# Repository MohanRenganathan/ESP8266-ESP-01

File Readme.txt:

This repository contains files related to ESP8266 model ESP-01

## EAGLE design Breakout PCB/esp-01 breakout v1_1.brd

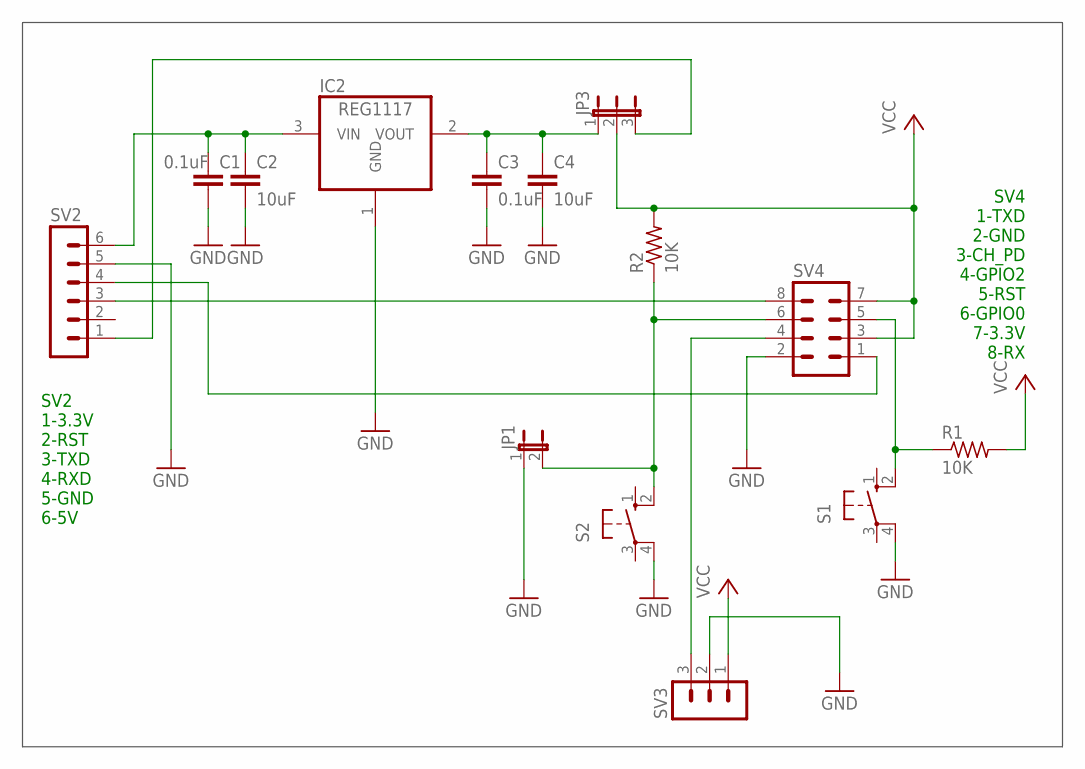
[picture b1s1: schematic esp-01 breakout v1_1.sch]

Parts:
C1, C3: 0.1uF; C025-025X050
C2, C4: 10uF; C025-025X050
IC2: REG1117; SOT223
JP1: JP1E; JP1
JP3: JP2E; JP2
R1, R2: 10K; 0207/7
S1, S2: 10-XX; B3F-10XX
SV2: MA06-1
SV3: MA03-1
SV4: MA04-2

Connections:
GND: C1.2, C2.2, C3.2, C4.2, IC2.1 (GND), JP1.1, S1.4 (P1), S2.4 (P1), SV2.5, SV3.2, SV4.2
unnamed: C1.1, C2.1, IC2.3 (VIN), SV2.6
unnamed: C3.1, C4.1, IC2.2 (VOUT), JP3.1
unnamed: JP3.3, SV2.1
unnamed: SV3.3, SV4.4
unnamed: R1.1, S1.2 (S1), SV4.5
unnamed: JP1.2, R2.1, S2.2 (S1), SV4.6
unnamed: SV2.3, SV4.8
unnamed: SV2.4, SV4.1
VCC: JP3.2, R1.2, R2.2, SV3.1, SV4.3, SV4.7

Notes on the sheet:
SV2 1-3.3V 2-RST 3-TXD 4-RXD 5-GND 6-5V
SV4 1-TXD 2-GND 3-CH_PD 4-GPIO2 5-RST 6-GPIO0 7-3.3V 8-RX

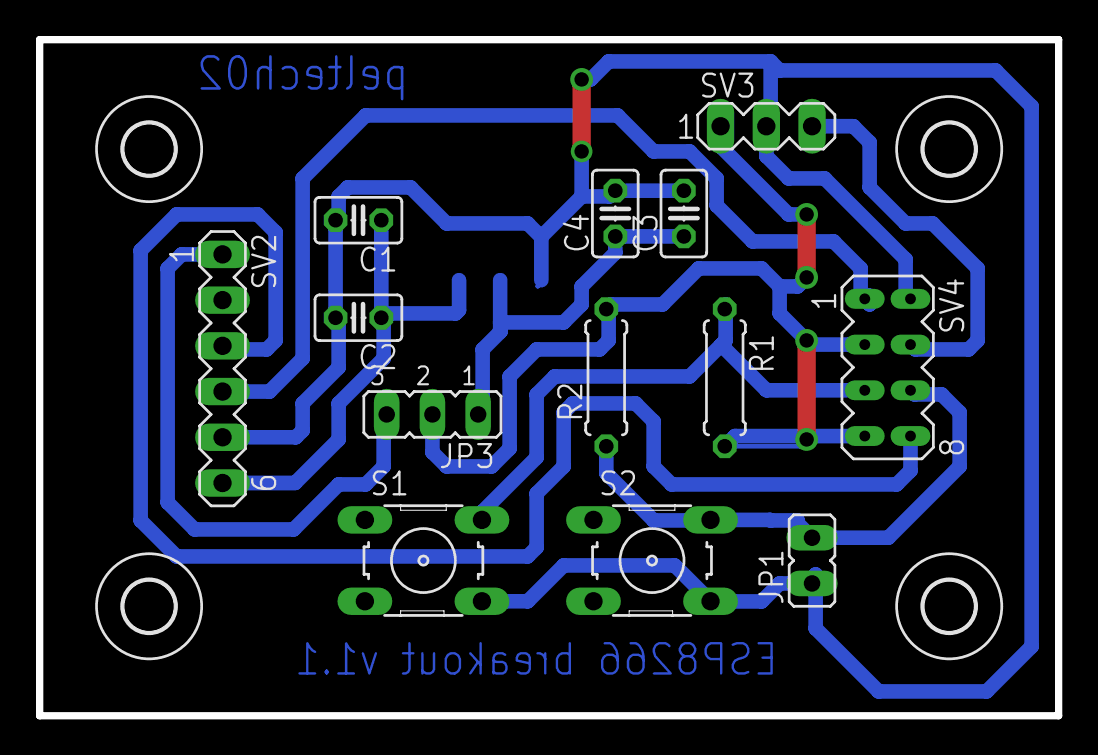
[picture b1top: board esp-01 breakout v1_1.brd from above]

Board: 2 copper layers, 56.6 x 37.6 mm, 18 parts (1 on the bottom side), 10 nets.

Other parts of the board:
U$1, U$2, U$3, U$4: 2,8

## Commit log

2015-04-11 :confetti_ball: Added .gitattributes & .gitignore files
2015-04-11 First commit
    Initial upload of all files
